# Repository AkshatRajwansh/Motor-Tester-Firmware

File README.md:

This firmware runs on an onboard Teensy 4.1 MCU in a custom designed PCB for an automated servo motor testing machine. You attach a servo, press a button, and it runs 10 tests automatically \- measuring position accuracy, speed, torque, stall point \- and reports everything on the OLED and over serial. 

### It's split into two phases: 
- Phase 1 (no load, pure motion tests) 
- Phase 2 (with a physical load touching the servo arm, torque/force tests).

Hardware Being Used -
| Device            | What it does in this project                                      |
|------------------|-------------------------------------------------------------------|
| AS5600           | Magnetic encoder \- reads the actual angle of the servo shaft      |
| INA219           | Current + voltage sensor \- measures what the servo is drawing     |
| HX711 + Load Cell| Measures force being applied to the servo arm                     |
| SSD1306 OLED     | 128x64 display \- shows live test status                           |
| SW1 Button       | User input \- advances between test phases                         |
| Servo PWM        | The servo motor being tested                                      |

The Custom Designed Schematic is as such - 

Here is a detailed explainantion of what is happening in each test and what will be displayed in the OLED screen as well as the serial monitor.

## Phase 1: No Load Tests

### Step 1 - Sweep Test
Moves servo 0°→180°→0° in 2° steps. Records angle, current, and timestamp at every step. Shows if the servo tracks commands accurately while moving and if current spikes at any specific angle.

**OLED Display:**
```
┌─────────────────────────┐
│       SWEEP TEST        │
│ Target:  90.0 deg       │
│ Actual:  89.7 deg       │
│ Current: 210.0 mA       │
│  │
└─────────────────────────┘
```

**Serial Output:**
```
══════════════════════════════════════════════
STEP 1: SWEEP TEST - Angle vs Time vs Current
══════════════════════════════════════════════
  t(ms)  | Target(°) | Actual(°) | Current(mA)
  -------|-----------|-----------|------------
       0 |      0.00 |      0.35 |      142.00
      22 |      2.00 |      2.11 |      198.00
      44 |      4.00 |      3.89 |      210.00
     ...
    1820 |    180.00 |    179.45 |      188.00
```

---

### Step 2 - Position Accuracy
Commands 5 angles (0°, 45°, 90°, 135°, 180°), waits for full settle, then reads actual angle. Computes `error = target - actual` for each. Reveals systematic bias or endpoint inaccuracy.

**OLED Display:**
```
┌─────────────────────────┐
│     POSITION TEST       │
│ Target:   90.0 deg      │
│ Actual:   89.9 deg      │
│ Error:   +0.10 deg      │
└─────────────────────────┘
```

**Serial Output:**
```
══════════════════════════════════════════════
STEP 2: POSITION ACCURACY
══════════════════════════════════════════════
  Target(°) | Actual(°) | Error(°)
  ----------|-----------|----------
       0.00 |      0.35 |   -0.350
      45.00 |     44.82 |   +0.180
      90.00 |     89.91 |   +0.090
     135.00 |    134.76 |   +0.240
     180.00 |    179.44 |   +0.560
  Max absolute error: 0.560°
```

---

### Step 3 - Repeatability
Moves to 90° seven times from 0° each time. Computes mean and standard deviation of the 7 readings. Low stdDev = tight mechanical consistency. High stdDev = backlash or gear play.

**OLED Display:**
```
┌─────────────────────────┐
│     Repeatability       │
│ Run 4: 89.921 deg       │
│ Target: 90 deg          │
└─────────────────────────┘
```

**Serial Output:**
```
══════════════════════════════════════════════
STEP 3: REPEATABILITY (target 90°)
══════════════════════════════════════════════
  Run 1: 89.912°    Run 5: 89.945°
  Run 2: 89.934°    Run 6: 89.908°
  Run 3: 89.898°    Run 7: 89.917°
  Run 4: 89.921°
  Mean:   89.919°
  StdDev: 0.0156°
  Range:  0.0470°
```

---

### Step 4 - Speed & Response
Commands 0°→90° and samples at high speed. Records rise time (how long to reach 90°), overshoot (how far past 90° it went), settling time (when it stops oscillating), and peak current.

**OLED Display:**
```
┌─────────────────────────┐
│       Speed Test        │
│ Ang:91.2  I:540mA       │
│ 0 -> 90 deg             │
└─────────────────────────┘
```

**Serial Output:**
```
══════════════════════════════════════════════
STEP 4: SPEED & RESPONSE (0° → 90°)
══════════════════════════════════════════════
  Rise time (to 90°):  210 ms
  Overshoot:           2.34°
  Settling time:       380 ms
  Peak current:        684.0 mA
```

---

## Phase 2: Load Tests

### Step 6 - Contact Detection
Moves forward slowly in 2° steps until load cell force exceeds threshold. Records the contact angle as the reference point for all torque tests.

**OLED Display:**
```
┌─────────────────────────┐
│     Contact Detect      │
│ Ang:22.0 F:4.2g         │
│ I: 145 mA               │
│ Moving forward...       │
└─────────────────────────┘
```

**Serial Output:**
```
══════════════════════════════════════════════
STEP 6: CONTACT DETECTION
══════════════════════════════════════════════
  Contact angle:  24.00°
  Contact force:  23.4 g
```

---

### Step 7 & 8 - Torque Map
From contact angle, pushes further in steps. At each step records force, angle, current, and voltage. Computes torque (`F × arm length`) and power (`V × I`). Reports peak torque angle with efficiency (`N·mm/mW`).

**OLED Display:**
```
┌─────────────────────────┐
│      TORQUE TEST        │
│ Ang: 36.0  I: 398mA     │
│ Force:   112.5 g        │
│ Torque:  55.18 N.mm     │
└─────────────────────────┘
```

**Serial Output:**
```
══════════════════════════════════════════════
STEP 7 & 8: TORQUE vs ANGLE vs CURRENT
══════════════════════════════════════════════
  Angle(°) | Force(g) | Torque(N·mm) | Current(mA) | Voltage(V) | Power(mW)
  ---------|----------|--------------|-------------|------------|----------
     24.00 |    23.40 |       11.481 |      198.00 |      4.980 |    986.04
     28.00 |    45.80 |       22.467 |      245.00 |      4.975 |   1218.88
     36.00 |   112.50 |       55.181 |      398.00 |      4.955 |   1972.09
     48.00 |   183.20 |       89.865 |      558.00 |      4.920 |   2745.36

  --- Peak Torque Point ---
  Angle:      48.00 deg
  Torque:     89.865 N·mm
  Current:    558.0 mA
  Voltage:    4.920 V
  Power:      2745.36 mW
  Efficiency: 0.0327 N·mm/mW
```

---

### Step 9 - Stall Test
Continues increasing load until both conditions trigger simultaneously: angle stops changing AND current spikes above threshold. Records stall torque, stall current, and stall angle.

**OLED Display:**
```
┌─────────────────────────┐
│       STALL TEST        │
│ Angle:   62.0 deg       │
│ Current:1342.0 mA       │
│ Torque: 118.45 N.mm     │
└─────────────────────────┘
```

**Serial Output:**
```
══════════════════════════════════════════════
STEP 9: STALL TEST
══════════════════════════════════════════════
  Stall angle:   62.00°
  Stall torque:  118.450 N·mm
  Stall current: 1342.0 mA
```

---

### Step 10 - Loaded Hold
Holds 90° for 3 seconds under load. Records position drift and current min/max/avg. Low drift + stable current = good servo. High drift or large current swings = weak holding or internal oscillation.

**OLED Display:**
```
┌─────────────────────────┐
│      TORQUE TEST        │
│ Ang: 89.9  I: 312mA     │
│ Force:    98.2 g        │
│ Torque:   48.16 N.mm    │
└─────────────────────────┘
```

**Serial Output:**
```
══════════════════════════════════════════════
STEP 10: LOADED HOLDING TEST
══════════════════════════════════════════════
  Hold angle:    90.00°
  End angle:     89.87°
  Drift:        -0.1300°
  Avg current:   312.4 mA
  Min current:   287.0 mA
  Max current:   341.0 mA
```

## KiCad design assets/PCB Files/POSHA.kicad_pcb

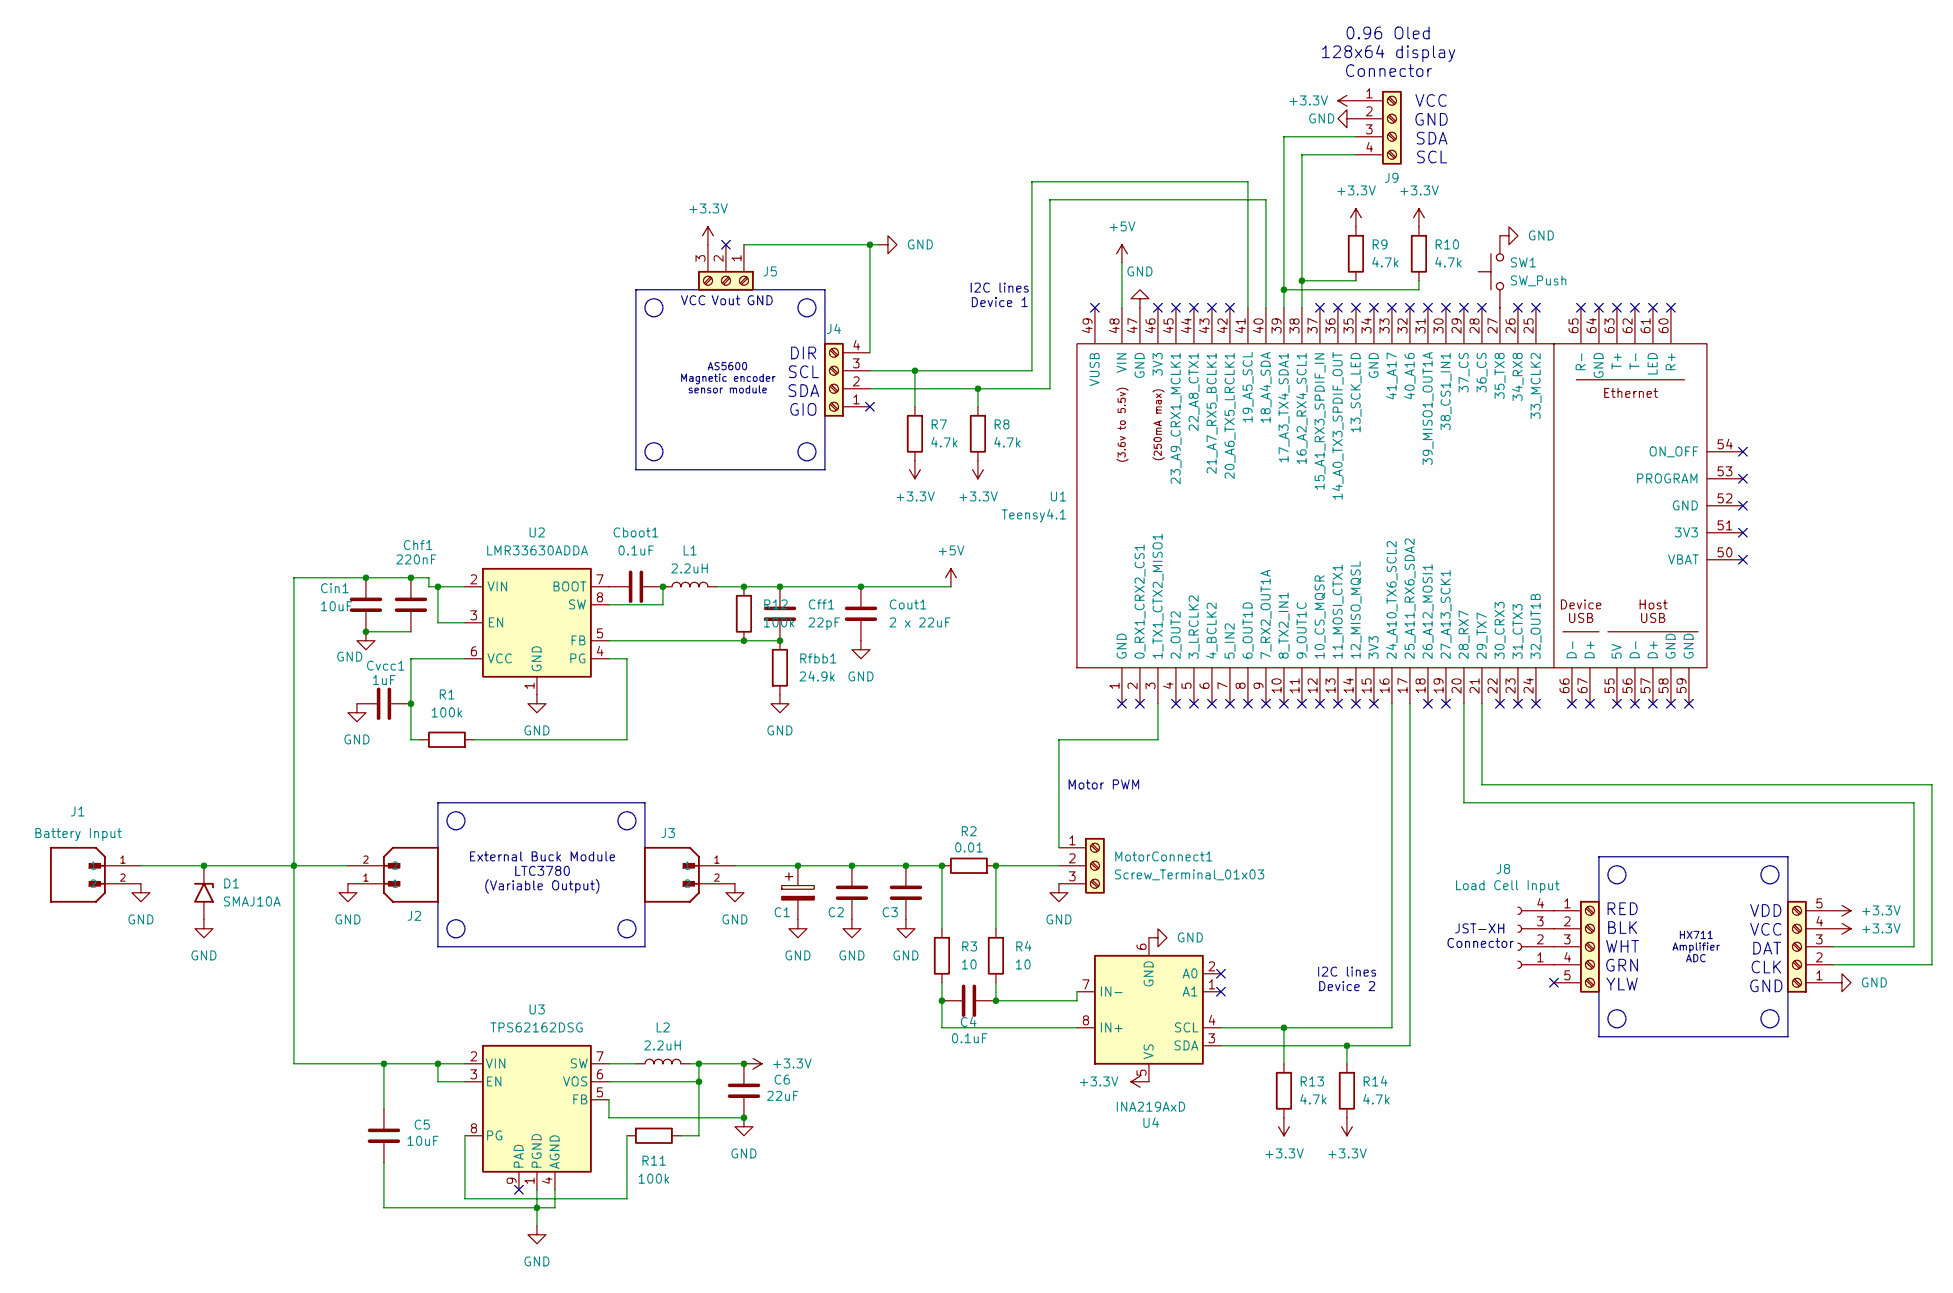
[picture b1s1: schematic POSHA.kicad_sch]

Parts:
C1: C_Polarized; C_2220_5750Metric_Pad1.97x5.40mm_HandSolder
C2, C3: C; C_2220_5750Metric_Pad1.97x5.40mm_HandSolder
C4: 0.1uF; C_0201_0603Metric
C5: 10uF; C_0201_0603Metric
C6: 22uF; C_0201_0603Metric
Cboot1: 0.1uF; C_0201_0603Metric
Cff1: 22pF; C_0201_0603Metric
Chf1: 220nF; C_0201_0603Metric
Cin1: 10uF; C_0201_0603Metric
Cout1: 2 x 22uF; C_0201_0603Metric
Cvcc1: 1uF; C_0201_0603Metric
D1: SMAJ10A; D_SMA
J1, J2, J3: Battery Input; AMASS_XT30U-F_1x02_P5.0mm_Vertical; PARTREV 1.2
J4, J9: Screw_Terminal_01x04; TerminalBlock_MaiXu_MX126-5.0-04P_1x04_P5.00mm
J5: Screw_Terminal_01x03; TerminalBlock_MaiXu_MX126-5.0-03P_1x03_P5.00mm
J6: Screw_Terminal_01x05; PinHeader_1x05_P1.00mm_Vertical
J7: Screw_Terminal_01x05; TerminalBlock_MaiXu_MX126-5.0-05P_1x05_P5.00mm
J8: Load Cell Input; JST_XH_B4B-XH-A_1x04_P2.50mm_Vertical
L1, L2: 2.2uH; L_Neosid_SM-NE127_HandSoldering
MotorConnect1: Screw_Terminal_01x03; TerminalBlock_MaiXu_MX126-5.0-03P_1x03_P5.00mm
R1, R11, R12: 100k; R_1210_3225Metric_Pad1.30x2.65mm_HandSolder
R2: 0.01; R_01005_0402Metric
R3, R4: 10; R_0201_0603Metric
R7, R8, R9, R10, R13, R14: 4.7k; R_1210_3225Metric
Rfbb1: 24.9k; R_0805_2012Metric
SW1: SW_Push; SW_PUSH_1P1T_6x3.5mm_H5.0_APEM_MJTP1250
U1: Teensy4.1; Teensy41
U2: LMR33630ADDA; Texas_HSOP-8-1EP_3.9x4.9mm_P1.27mm_ThermalVias
U3: TPS62162DSG; WSON-8-1EP_2x2mm_P0.5mm_EP0.9x1.6mm_ThermalVias
U4: INA219AxD; SOIC-8_3.9x4.9mm_P1.27mm

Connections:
+3.3V: C6.1, J5.3, J6.4, J6.5, J9.1, L2.2, R7.1, R8.1, R9.2, R10.2, R11.1, R13.1, R14.1, U3.6 (VOS), U4.5 (VS)
+5V: Cff1.1, Cout1.1, L1.2, R12.2, U1.48 (VIN)
GND: C1.2, C2.2, C3.2, C5.2, C6.2, Chf1.2, Cin1.2, Cout1.2, Cvcc1.2, D1.2 (A2), J1.2, J2.1, J3.2, J4.4, J5.1, J6.1, J9.2, MotorConnect1.3, Rfbb1.2, SW1.2, U1.47 (GND), U2.1 (GND), U2.9 (GND), U3.1 (PGND), U3.4 (AGND), U3.5 (FB), U4.6 (GND)
unnamed: C1.1, C2.1, C3.1, J3.1, R2.1, R3.2
unnamed: C5.1, Chf1.1, Cin1.1, D1.1 (A1), J1.1, J2.2, U2.2 (VIN), U2.3 (EN), U3.2 (VIN), U3.3 (EN)
unnamed: J4.2, R8.2, U1.40 (18_A4_SDA)
unnamed: J4.3, R7.2, U1.41 (19_A5_SCL)
unnamed: J6.2, U1.21 (29_TX7)
unnamed: J6.3, U1.20 (28_RX7)
unnamed: J7.1, J8.4
unnamed: J7.2, J8.3
unnamed: J7.3, J8.2
unnamed: J7.4, J8.1
unnamed: J9.3, R10.1, U1.39 (17_A3_TX4_SDA1)
unnamed: J9.4, R9.1, U1.38 (16_A2_RX4_SCL1)
unnamed: MotorConnect1.1, U1.3 (1_TX1_CTX2_MISO1)
unnamed: MotorConnect1.2, R2.2, R4.2
unnamed: R13.2, U1.16 (24_A10_TX6_SCL2), U4.4 (SCL)
unnamed: R14.2, U1.17 (25_A11_RX6_SDA2), U4.3 (SDA)
unnamed: SW1.1, U1.27 (35_TX8)
unnamed: Cboot1.1, U2.7 (BOOT)
unnamed: Cff1.2, R12.1, Rfbb1.1, U2.5 (FB)
unnamed: R1.2, U2.4 (PG)
unnamed: Cboot1.2, L1.1, U2.8 (SW)
unnamed: Cvcc1.1, R1.1, U2.6 (VCC)
unnamed: R11.2, U3.8 (PG)
unnamed: L2.1, U3.7 (SW)
unnamed: C4.1, R3.1, U4.8 (IN+)
unnamed: C4.2, R4.1, U4.7 (IN-)

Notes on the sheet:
Vout
I2C lines Device 1
VCC
Motor PWM
AS5600 Magnetic encoder sensor module
0.96 Oled 128x64 display Connector
JST-XH Connector
DIR SCL SDA GIO
RED BLK WHT GRN YLW
VDD VCC DAT CLK GND
GND
External Buck Module LTC3780 (Variable Output)
I2C lines Device 2
HX711 Amplifier ADC
VCC GND SDA SCL

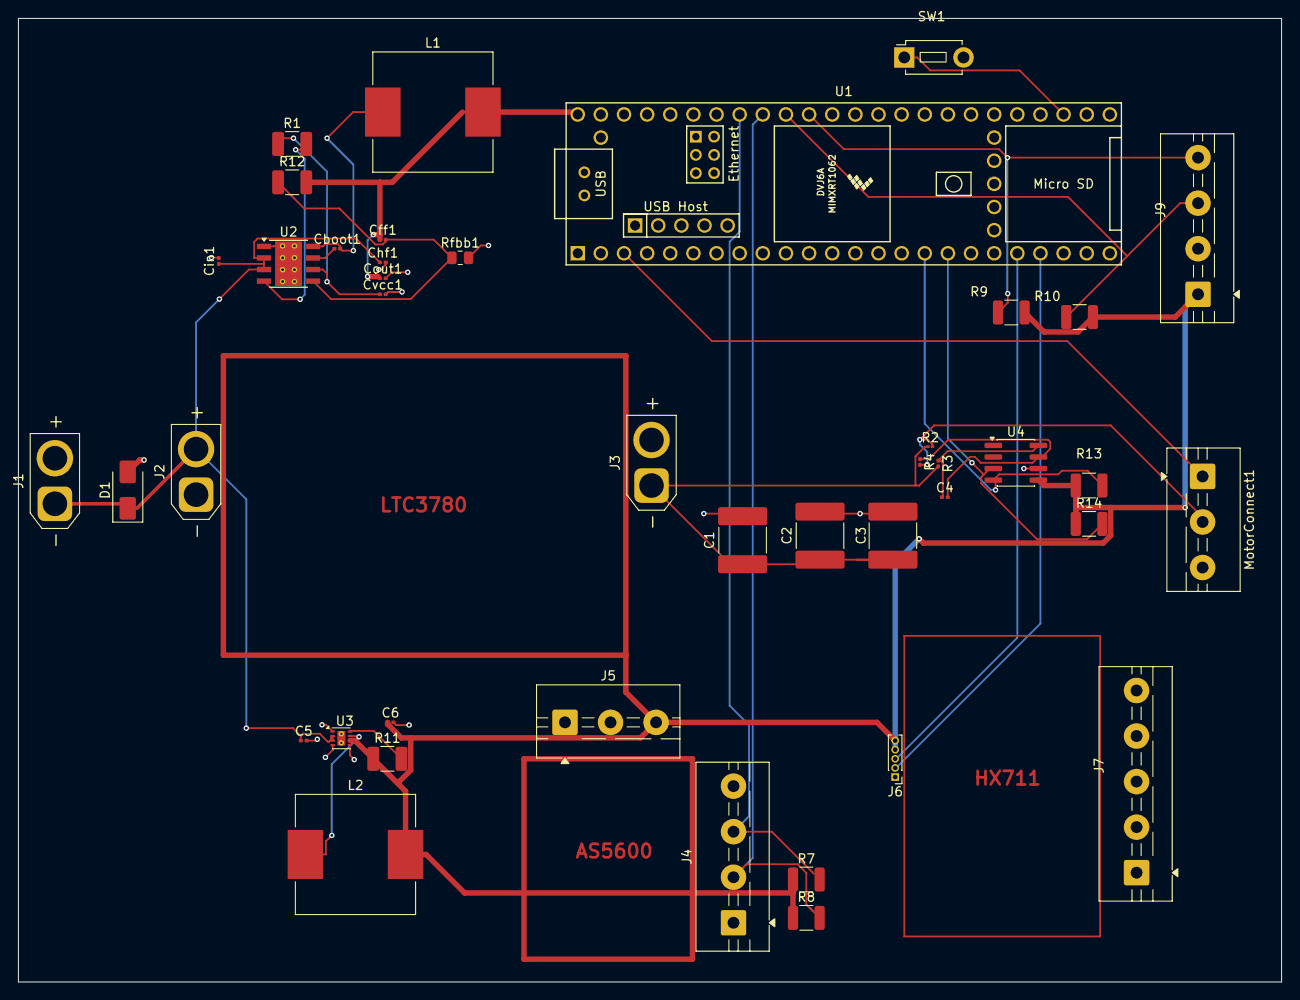
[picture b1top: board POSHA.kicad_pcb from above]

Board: 2 copper layers, 138.7 x 105.8 mm, 42 parts (0 on the bottom side), 25 nets.

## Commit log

2026-03-29 Moved OLED to seperate wire
2026-03-29 Modified Display manager
2026-03-29 Added schematic file and fixed display error
2026-03-29 Rename POSHA.kicad_sch to ControlBoard.kicad_sch
2026-03-29 Final changes
2026-03-29 Modified result calculation and added PCB Current Status
2026-03-30 Added PCB Files
2026-03-30 Added Jig Design Sketch
